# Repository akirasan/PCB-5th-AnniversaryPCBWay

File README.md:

# Badge PCB 5th Anniversary of PCBWay
The badge of 5th Anniversary PCBWay
http://www.pcbway.com

The project is share on
https://www.pcbway.com/project/shareproject/5th_Anniversary_badge.html

Design with opensource tools: #Inkscape and #KiCAD

I have use #Blender for differents renders on 3D

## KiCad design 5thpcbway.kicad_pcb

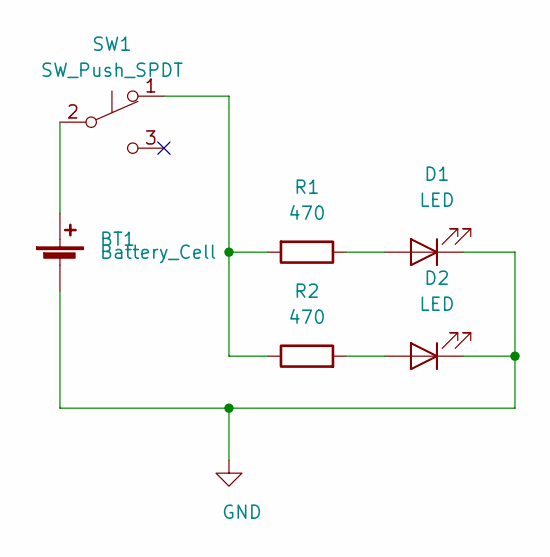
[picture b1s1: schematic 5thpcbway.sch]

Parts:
BT1: Battery_Cell; BatteryHolder_Keystone_3034_1x20mm
D1, D2: LED; LED_RGB_0807_2012Metric_HandSolder
R1, R2: 470; R_0805_2012Metric_Pad1.15x1.40mm_HandSolder
SW1: SW_Push_SPDT; SW_SPDT_PCM12

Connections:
GND: BT1.2 (-), D1.1 (K), D2.1 (K)
unnamed: BT1.1 (+), SW1.2 (B)
unnamed: D1.2 (A), R1.1
unnamed: D2.2 (A), R2.2
unnamed: R1.2, R2.1, SW1.1 (A)

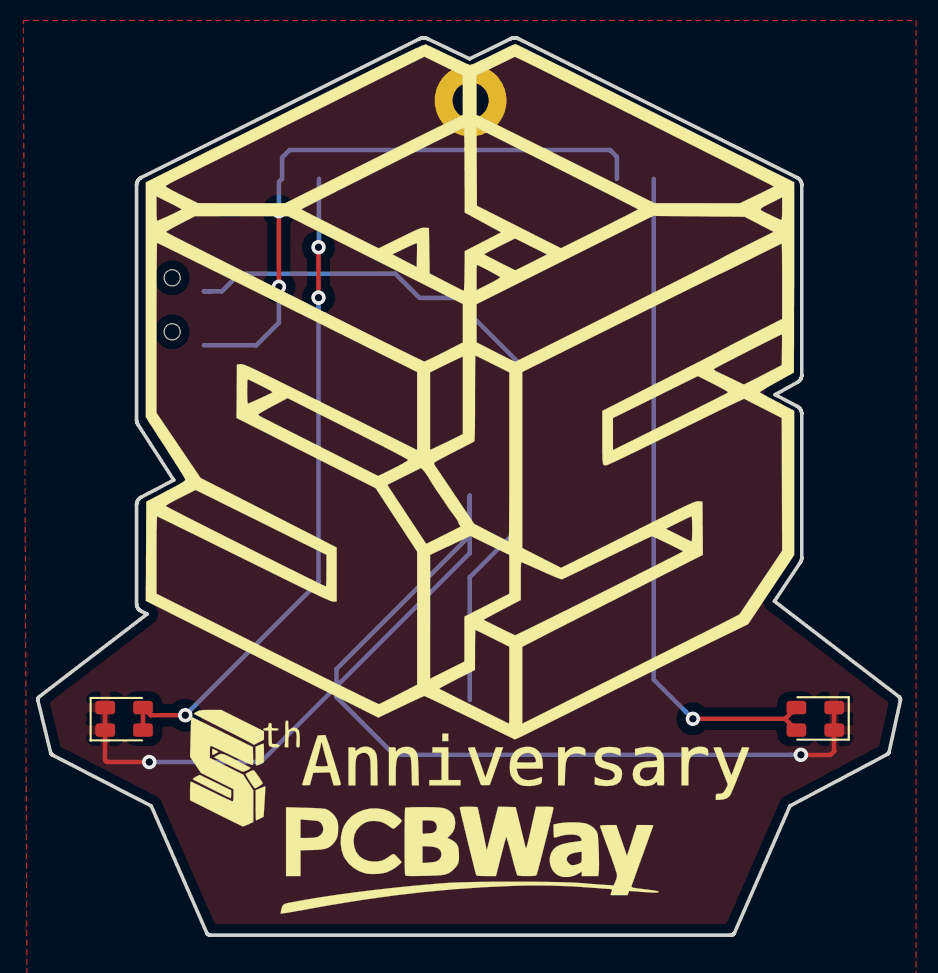
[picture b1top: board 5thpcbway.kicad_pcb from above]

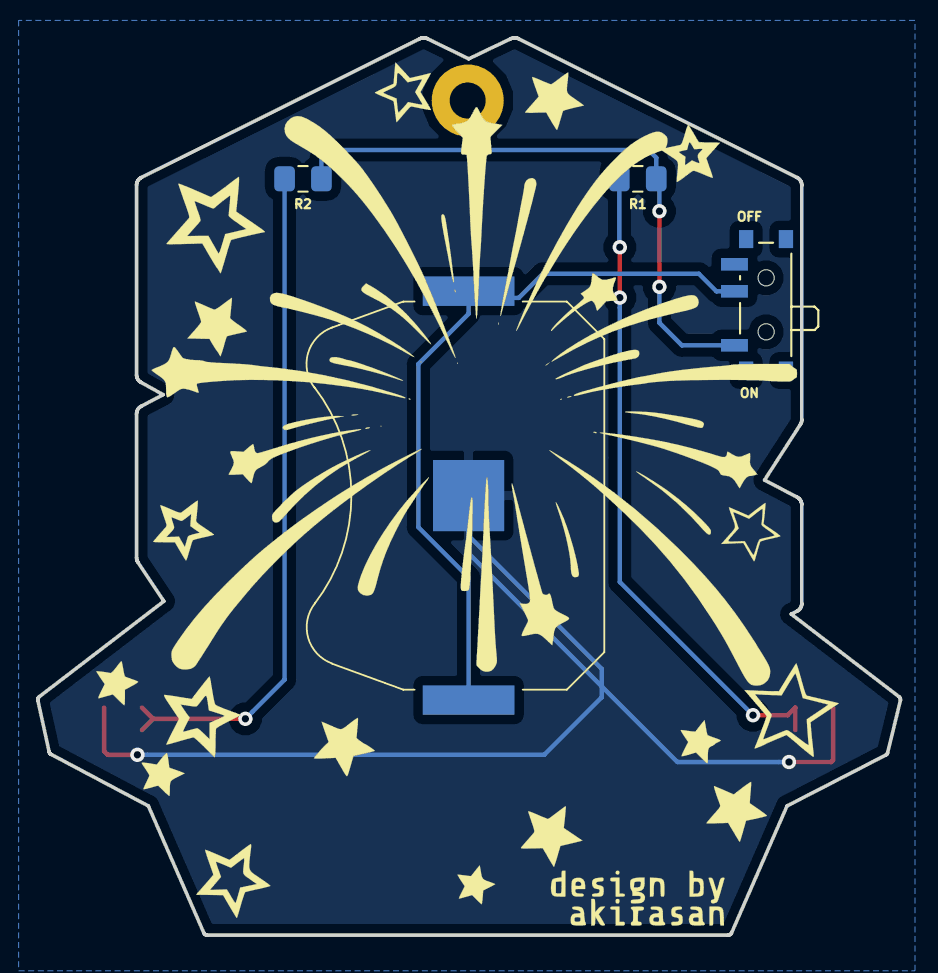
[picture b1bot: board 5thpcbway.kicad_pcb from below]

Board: 2 copper layers, 47.9 x 49.9 mm, 6 parts (4 on the bottom side), 5 nets.

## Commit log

2019-06-18 Initial upload
